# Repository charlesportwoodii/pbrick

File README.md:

<div align="center">

  <h1>PBRICK</h1>

  <p>
    <strong>A USB-C PD powered, Bluetooh controlled motor driver and IO software and hardware.</strong>
  </p>
  <hr />
</div>

## About
PBrick is a personal project born out of a desire to learn Kicad, and develop embedded software, learn USB-C PD, and create a full end-to-end software solutions. I currently use pbrick to power a few custom toys, and other things that require motor driver for toys and gadgets.

While I won't call this "battle-tested" hardware and software, I have successfully manufactured and used it for over a year now without problem or incident.

This board has been in various stages of development since 2018, and has been significantly impacted by the semi-conductor supply chain.

## Features

- Dual motor driver for powering two separate motors independently, up to 20V5A (100W of power), and 12V3A per rail
- Dual motor driver ouputs on rear of board with input power output rails + GND
- USB-C Power Delivery (PD) input
- Configurable JST-2 pin connector for either PD output when using USB-C PD, or direct power input with backfeed protection
    (You may power the board either by USB-PD or by this PIN)
- i2c output on rear of board for running and powering additional accessories
- Programmable LED Status light
- Single button with double tap to reset functionality available in the [Kaidyth Bootloader](https://github.com/kaidyth/nrf52_bootloader)
- Accelerometer for rollover detection
- 4 Layer board with dedicated GND layer

## Board Pictures

<div align="center">

  <br />

</div>

## Schematic
The current schematic is available at https://github.com/charlesportwoodii/pbrick/blob/TB67H420FTG-24MM-C-a/board/schematic.pdf.

## Revisions
There are a number of revisions to the board. The active branch is `TB67H420FTG-24MM-C-a` .

## Production Notes
COVID-19 continues to cause part shortages, and I cannot currently provide any guarantees or alternative parts. Here's a few notes from my production of this revision of the board should you choose to make it yourself.

- I'd recommend OshPark + Osh Stencils to create the board and the stencil. Use a heat gun for soldering, then hand solder the external connections.
- After soldering and verifying all the components, I strongly recommend super-gluing the USB-C port directly to the board at the connection points. It's not difficult to break the connection by accident with just solder.
- You may ommit the accelerometer, and any i2c components depending upon available.
- The board should stay fairly cool even when running multiple motors on the same channel. If the board starts to rapidly heat up I am almost guarantee you have a bridge on the motor pins.
- I strongly recommend adding additional solder to JP1 bridge that connects VSS to VDD (see schematic). Be generous and liberal as this is the main power bus. The Jumper is used here as there is an alternative configuration where it can be cut and the board can be powered from one of the outputs but that's not supported yet so don't do it.
- Despite the abundance of USB-C PD devices on Amazon _a lot_ of them don't actually support USB-C PD (most really only provide proprietary protocols). The best I've found is [XCentz 5000mAh Charger](https://www.amazon.com/gp/product/B07LB18B73/ref=ppx_yo_dt_b_search_asin_title?ie=UTF8&psc=1) but again, COVID has made stock + availability intermittent.
- You'll probably want a very short USB-C PD cable. The shortest I've found is: https://www.amazon.com/gp/product/B08L8Z7YJ8/ref=ppx_yo_dt_b_search_asin_title?ie=UTF8&psc=1.
- Q1 and Q2 will protect any backfeed current from J5 _however_ if you're going to power the board over J5, I would completely omit the USB-C PD section of the board, and cut JP1 to prevent power flowing to that entire section of the board.

## Functionality Notes

- Currently there's no software to measure or control the accelerometer due to stock and availability. I simply have never been able to source the part. The intent with the accelerometer is to provide "rollover" detection in the event the object/toy falls off the track or rolls over or experiences a significant G force event so that the power to the motors can be either momentarily or permanently cut.
- You can use the nRF Connect app to send the payload to the Motor service. The payload is a 3 byte serial, <MOTOR><SPEED><DIRECTION>
Motor selection being 00, and 01 for the respective board MX, the "speed" value being the PWM speed from 00-64 (anything greater than 64 is considered 64), and the direction parameter which will set the motor direction. There's a special mode 0x02 and 0x03 which will cause both motors to run at the same speed + PWM either in the same, or in opposite directions if you need to syncronize them. Feel free to play around with the inputs.
- Flash the board with both the Kaidyth Bootloader, and a compiled version so that you have full DFU support. Using other bootloaders will result in error.

## License

PBRICK is currently source-available. For non-commercial scientific research, non-commercial education, or non-commercial artistic projects, PBRICK is available under the BSD-3 Clause license. No commercial license is permitted whatsoever.

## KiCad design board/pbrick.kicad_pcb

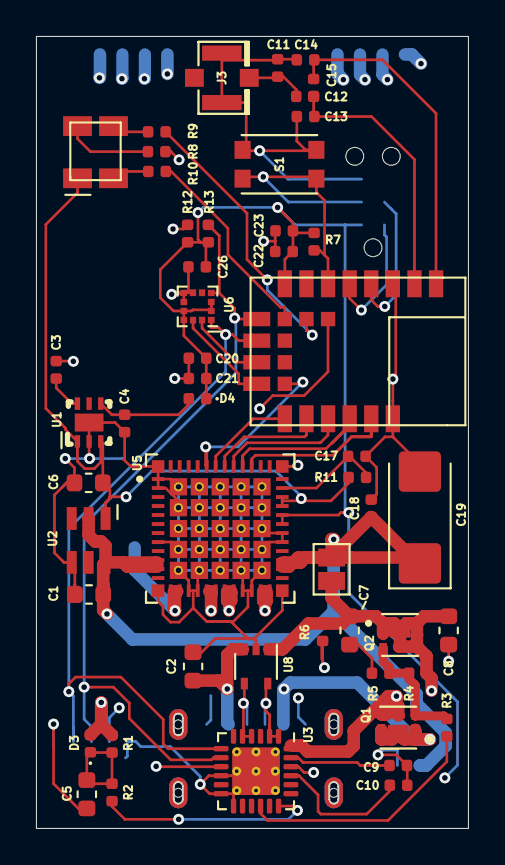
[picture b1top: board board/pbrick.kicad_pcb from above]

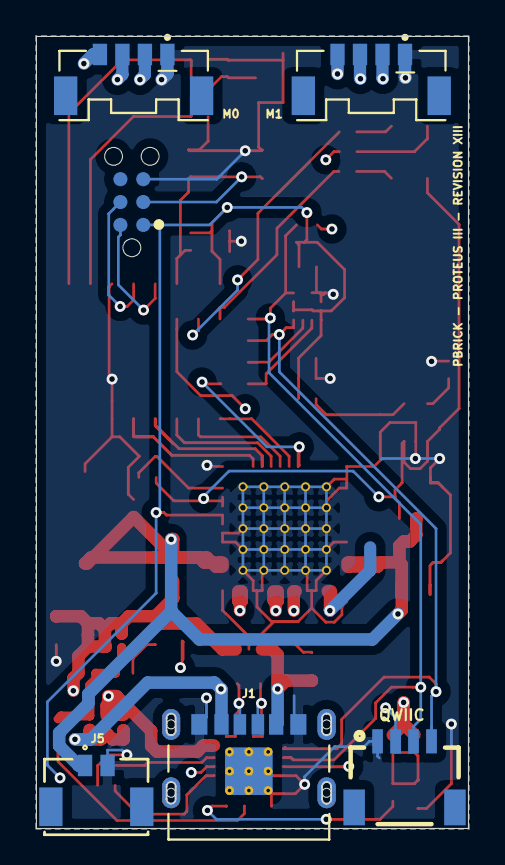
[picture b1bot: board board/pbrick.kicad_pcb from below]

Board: 4 copper layers, 24.0 x 44.0 mm, 57 parts (6 on the bottom side), 45 nets.

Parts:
C1, C6: 470nF 0603; C_0603_1608Metric
C2: 4.7uF 0603; C_0603_1608Metric
C3: 470pF 0402; C_0402_1005Metric
C4: 2.2uF 0402; C_0402_1005Metric
C5, C8: 1uF 0603; C_0603_1608Metric
C7: 100nF 0603; C_0603_1608Metric
C9, C10, C22: 1uF 0402; C_0402_1005Metric
C11, C12, C13, C14, C15: 22pF 0402; C_0402_1005Metric
C17: 270pF 0402; C_0402_1005Metric
C18, C20, C21, C23, C26: 100nF 0402; C_0402_1005Metric
C19: 22UF 10% 25V; CP_EIA-6032-15_Kemet-U_Pad2.25x2.35mm_HandSolder
D3, D4: D_Schottky; D_0402_1005Metric
J1: UJC-HP-3-SMT-TR; CUI_UJC-HP-3-SMT-TR
J2: TC2030-IDC-NL; TAG_TC2030-IDC-NL
J3: U.FL2PIN; U.FL
J4: QWIIC; 1X04_1MM_RA
J5: 5055670271
JP1: SolderJumper_2_Bridged; SolderJumper-2_P1.3mm_Open_Pad1.0x1.5mm
LED1: 150121M153000
M0, M1: 5055680471; MOLEX_5055680471
PROTEUS-III1: PROTEUS-III; WIRL-BLTE_Proteus-III
Q1, Q2: SSM6J507NU; TRANS_SSM6J507NU,LF
R1: 470 Ω 0402; R_0402_1005Metric
R2, R6: 1K Ω 0402; R_0402_1005Metric
R3: 22K Ω 0402; R_0402_1005Metric
R4: 100K Ω 0402; R_0402_1005Metric
R5: 100 Ω 0402; R_0402_1005Metric
R7: 10K 0402; R_0402_1005Metric
R8, R9: 85 Ω 0402; R_0402_1005Metric
R10: 140 Ω 0402; R_0402_1005Metric
R11: 5.1K; R_0402_1005Metric
R12, R13: 2.2K Ω 0402; R_0402_1005Metric
S1: KMR621NGLFS; SW_KMR621NGLFS
U1: MIC5219-3.3YML-TR; QFN6_THERMAL_PAD
U2: ADP3330ARTZ-5-RL7; SOT95P280X145-6N
U3: STUSB4500QTR; QFN-24-1EP_4x4mm_P0.5mm_EP2.65x2.65mm_ThermalVias
U5: TB67H420FTG(O,EL); IC_TB67H420FTG(O,EL)
U6: 2533020201601; LGA-12_2x2mm_P0.5mm
U8: ESDA25W5; SOT-353_SC-70-5

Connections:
3.3V: C20.2, C21.2, C22.1, C23.1, C26.2, D4.1, J2.1, J4.2, PROTEUS-III1.8, R7.1, R12.1, R13.2, U3.22, U5.31, U5.32, U6.2, U6.3, U6.9, U6.10
5V: C6.1, LED1.4, R11.1, U1.1, U1.3, U2.1, U5.33, U5.34
/ANT: C14.2, C15.1, PROTEUS-III1.1
/DISCH: R6.2, U3.9
/M0_0: M0.3, U5.19, U5.20
/M0_1: M0.2, U5.23, U5.24
/M1_0: M1.2, U5.17, U5.18
/M1_1: M1.3, U5.13, U5.14
/P0.00: PROTEUS-III1.11, U6.12
/P0.01: PROTEUS-III1.12, U6.11
/P0.03: PROTEUS-III1.17, U5.39
/P0.07: PROTEUS-III1.B6, U5.44
/P0.09: PROTEUS-III1.B1, R8.2
/P0.10: PROTEUS-III1.B2, R9.2
/P0.11: PROTEUS-III1.15, U5.41
/P0.12: PROTEUS-III1.16, U5.40
/P0.18: J2.3, PROTEUS-III1.6, R7.2, S1.2_1, S1.2_2
/P0.19: J4.3, PROTEUS-III1.9, R13.1, U3.8, U6.4
/P0.22: J4.4, PROTEUS-III1.10, R12.2, U3.7, U6.1
/P0.23: PROTEUS-III1.B3, R10.2
/P1.08: PROTEUS-III1.13, U5.43
/P1.09: PROTEUS-III1.14, U5.42
/RF: C12.1, C13.1, C15.2, PROTEUS-III1.2
/SWDCLK: J2.4, PROTEUS-III1.4
/SWDIO: J2.2, PROTEUS-III1.5
/VBUS_EN_SNK: R3.2, U3.16
GND: C1.2, C2.2, C3.1, C4.2, C5.2, C6.2, C8.1, C9.1, C10.1, C11.1, C13.2, C14.1, C17.1, C18.1, C19.2, C20.1, C21.1, C22.2, C23.2, C26.1, J1.A12, J1.B12, J2.5, J3.1, J3.2, J4.1, J5.2, M0.1, M1.1, PROTEUS-III1.3, PROTEUS-III1.18, S1.1_1, S1.1_2, U1.2, U2.4, U3.10, U3.12, U3.13, U3.25, U5.1, U5.2, U5.8, U5.15, U5.16, U5.21, U5.22, U5.29, U5.30, U5.49, U5.50, U5.51, U5.52, U5.53, U5.54, U5.55, U5.56, U5.57, U5.58, U5.59, U5.60, U5.61, U5.62, U5.63, U5.64, U5.65, U5.66, U5.67, U5.68, U5.69, U5.70, U5.71, U5.72, U5.73, U5.74, U5.75, U5.76, U5.77, U5.78, U5.79, U5.80, U5.81, U5.82, U5.83, U5.84, U5.85, U5.86, U5.87, U5.88, U5.89, U5.90, U5.91, U5.92, U5.93, U5.94, U5.95, U5.96, U5.97, U5.98, U5.G1, U5.G2, U5.G3, U5.G4, U6.6, U6.7, U6.8, U8.2
unnamed: C3.2, U1.6
unnamed: C4.1, D4.2, U1.4
unnamed: C5.1, D3.1, R1.1, R2.1
unnamed: C7.2, R5.1
unnamed: C9.2, U3.23
unnamed: C10.2, U3.21
unnamed: C11.2, C12.2, J3.FEED
unnamed: C17.2, R11.2, U5.35
unnamed: J1.A5, U3.1, U3.2, U8.5
unnamed: J1.B5, U3.4, U3.5, U8.4
unnamed: LED1.1, R10.1
unnamed: LED1.2, R9.1
unnamed: LED1.3, R8.1
unnamed: Q1.3, Q2.3, R3.1, R4.2, R5.2
unnamed: R2.2, U3.18
VBUS: C2.1, D3.2, J1.A9, J1.B9, Q1.1, Q1.2, Q1.5, Q1.6, Q1.7, R1.2, U8.3
VDD: C1.1, C18.2, C19.1, J5.1, JP1.2, M0.4, M1.4, U2.2, U2.6, U5.10, U5.11, U5.26, U5.27
VSS: C7.1, C8.2, JP1.1, Q1.4, Q1.8, Q2.1, Q2.2, Q2.4, Q2.5, Q2.6, Q2.7, Q2.8, R4.1, R6.1, U3.24, U8.1

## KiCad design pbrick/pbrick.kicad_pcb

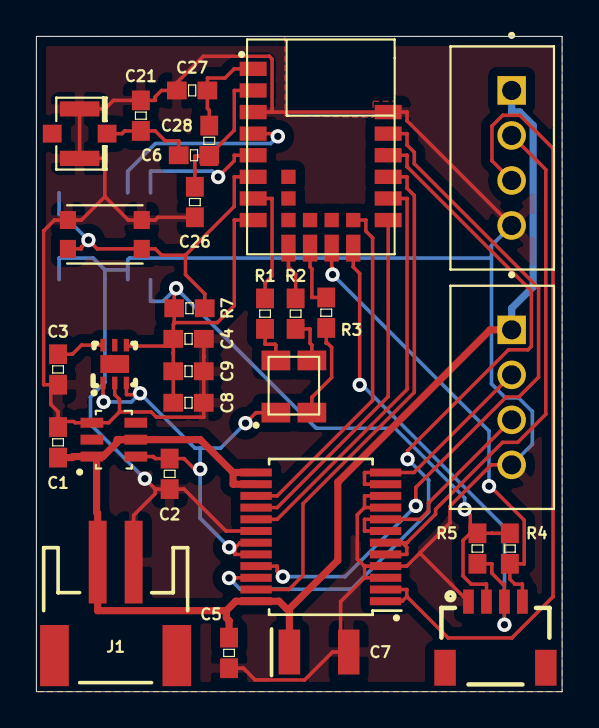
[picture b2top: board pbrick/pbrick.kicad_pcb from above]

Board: 2 copper layers, 29.2 x 36.4 mm, 31 parts (1 on the bottom side), 29 nets.

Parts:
C1, C2: 470nF 0603; 0603
C3: 470pF; 0603
C4: 2.2uf; 0603
C5: .22uF; 0603
C6, C21, C26, C27, C28: 22pF 0603; 0603
C7: 16V 10uF; EIA3528
C8: 100nF 0603; 0603
C9: 1uF 0603; 0603
J1: JST_2MM_MALE; JST-2-SMD
J2: QWIIC; 1X04_1MM_RA
J3, J4: B4B-XH-A(LF)(SN); JST_B4B-XH-A(LF)(SN)
J5: U.FL2PIN; U.FL
LED1: 150121M153000
P0: SWD; SAMTECH_FTSH-105-01
PROTEUS-III1: PROTEUS-III; WIRL-BLTE_Proteus-III
R1, R2: 85 Ω 0603; 0603
R3: 140 Ω 0603; 0603
R4, R5: 2.2K Ω 0603; 0603
R7: 10K 0603; 0603
S1: KMR621NGLFS; SW_KMR621NGLFS
U1: ADP3330ARTZ-5-RL7; SOT95P280X145-6N
U2: MIC5219-3.3YML-TR; QFN6_THERMAL_PAD
U3: TB6612FNG; SSOP-24_5.3x8.2mm_P0.65mm

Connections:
3.3V: C4.1, C8.1, C9.1, J2.2, P0.1, PROTEUS-III1.8, R4.1, R5.2, R7.1, U2.4
5V: C2.1, LED1.4, U1.1, U2.1, U2.3, U3.19, U3.20
/ANT: C27.2, C28.1, PROTEUS-III1.1
/M0_0: J3.3, U3.1, U3.2
/M0_1: J3.2, U3.5, U3.6
/M1_0: J4.2, U3.11, U3.12
/M1_1: J4.3, U3.7, U3.8
/P0.00: J2.4, PROTEUS-III1.11, R4.2
/P0.01: J2.3, PROTEUS-III1.12, R5.1
/P0.02: PROTEUS-III1.7, R1.2
/P0.03: PROTEUS-III1.17, U3.21
/P0.07: PROTEUS-III1.B6, U3.15
/P0.11: PROTEUS-III1.15, U3.23
/P0.12: PROTEUS-III1.16, U3.22
/P0.18: P0.10, PROTEUS-III1.6, R7.2, S1.2_1, S1.2_2
/P0.19: PROTEUS-III1.9, R2.2
/P0.22: PROTEUS-III1.10, R3.2
/P1.08: PROTEUS-III1.13, U3.16
/P1.09: PROTEUS-III1.14, U3.17
/RF: C6.1, C26.1, C28.2, PROTEUS-III1.2
/SWDCLK: P0.4, PROTEUS-III1.4
/SWDIO: P0.2, PROTEUS-III1.5
Earth: C1.2, C2.2, C3.1, C4.2, C5.1, C7.C, C8.2, C9.2, C21.1, C26.2, C27.1, J1.1, J2.1, J3.4, J4.4, J5.1, J5.2, P0.3, P0.5, P0.9, PROTEUS-III1.3, PROTEUS-III1.18, S1.1_1, S1.1_2, U1.4, U2.2, U3.3, U3.4, U3.9, U3.10, U3.18
unnamed: C3.2, U2.6
unnamed: C6.2, C21.2, J5.FEED
unnamed: LED1.1, R3.1
unnamed: LED1.2, R2.1
unnamed: LED1.3, R1.1
VDD: C1.1, C5.2, C7.A, J1.2, J3.1, J4.1, U1.2, U1.6, U3.13, U3.14, U3.24

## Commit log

2020-12-21 Merging board source code with firmware
2020-12-21 Missing directory
2020-12-21 Removing submodule
2020-12-21 Adding firmware
2020-12-31 non-16mm
2020-12-31 removing extra copper
2020-12-31 Converting to 24mm x 45mm board
2021-01-23 Updating board bSilk, pin definitions
2021-01-23 Updating board
2021-01-31 Type-C built-in power
2021-01-31 USB-PD Type-C Support
2021-02-01 Updating 3D model
2021-02-02 Adding new symbols
2021-02-02 TD2030 pin connector instead of CotexDebug, routable path
2021-02-02 New board fill
2021-02-03 Starting work on STUSB4500 USB i2C connection for new board design
2021-02-04 Initialize TWI - Currently stuck on nrf_drv_twi_tx #78 not executing completing in async mode
2021-02-04 TWI in blocking model successfully initializes STUSB4500 - @todo: Implement 9V2A switch and verify PDO output
2021-02-07 Working STUSB4500 i2c interface
2021-02-07 Fixing router keepout zone issue with vias
2021-02-22 Added 3-axis sensor Added dedicate PWM driver Added 2 MOLEX connectors 3x5 (24mm x 40mm)
2021-02-23 Updating footprints
2021-02-23 Outpitting basic info
2021-02-23 Updating parts list
2021-02-23 Minor part update
2021-03-07 Adding BOM information for PCA9632BS
2021-03-07 Fixes design defect with 0402 resistor pads Adds NXP LED driver DigiKey Part information for ordering Adds more space for SWD connector Spaces out QWIIC and USB-C connector
2021-03-08 Correct schematic defect where Q2 was not routed on both ends
2021-03-09 Adding option for exposing PDO profile options
2021-03-11 5v regulator has operational capacity from 2.7-20v (tested) - removing extra diode and 2.7v line as 5v => 3.3v works at 5v input
2021-03-11 Updating PCB routing
2021-03-11 Updating PCB layout
2021-03-22 Updating PCB to resolve an issue with PCA9624 OE being HIGH instead of Controller - Added PCA9624 library definition (untested) - Convert pbrick_motor to use PCA9624 driver
2021-03-22 Minor code cleanup
2021-03-28 Updating layout
2021-03-28 Updating board, definitions
2021-03-28 Cleanup
2021-03-28 Updating PCB
2021-03-30 Updating part list. Missing alt 12v connector
2021-03-31 Adding extra vin, manual routing
2021-04-01 Unfillfing zones
2021-04-01 New routing
2021-04-01 Updating Board, schematic, generated files
2021-04-02 Minor board layout update
2021-04-18 PCA9642 nonfunctional on board
2021-04-18 PCA9685 instead of PCA42
2021-04-18 Revision XI for PCA9685
2021-04-18 Initial work on PCA9685
2021-04-18 Adding PCA9685 library for testing
2021-04-18 Simple interface for testing
2021-04-18 Allow BLE not to crash if PCA9685 isn't connected
2021-04-27 PCA9624 still doesn't work
2021-06-03 Reverting to APP_PWM from board
2021-06-19 Wrong board wiring again...
2021-06-19 Removing debug code
2021-06-20 Minor board update
2021-06-20 Minor wire change
2021-07-11 Updating Board layout, pcb, board definition
2021-12-03 Updating board layout to align with other PF modules - Swapped GND and VDD on M0 and M0 to avoid wire crossing in cable wiring (external) - Swapped M1_0 and M1_1 to eliminate trace crossover (will so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
2022-10-08 License, README, + more pictures
2022-10-08 speling

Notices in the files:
parts and their libraries:
Copyright 2016 Accelerated Designs. All rights reserved.
